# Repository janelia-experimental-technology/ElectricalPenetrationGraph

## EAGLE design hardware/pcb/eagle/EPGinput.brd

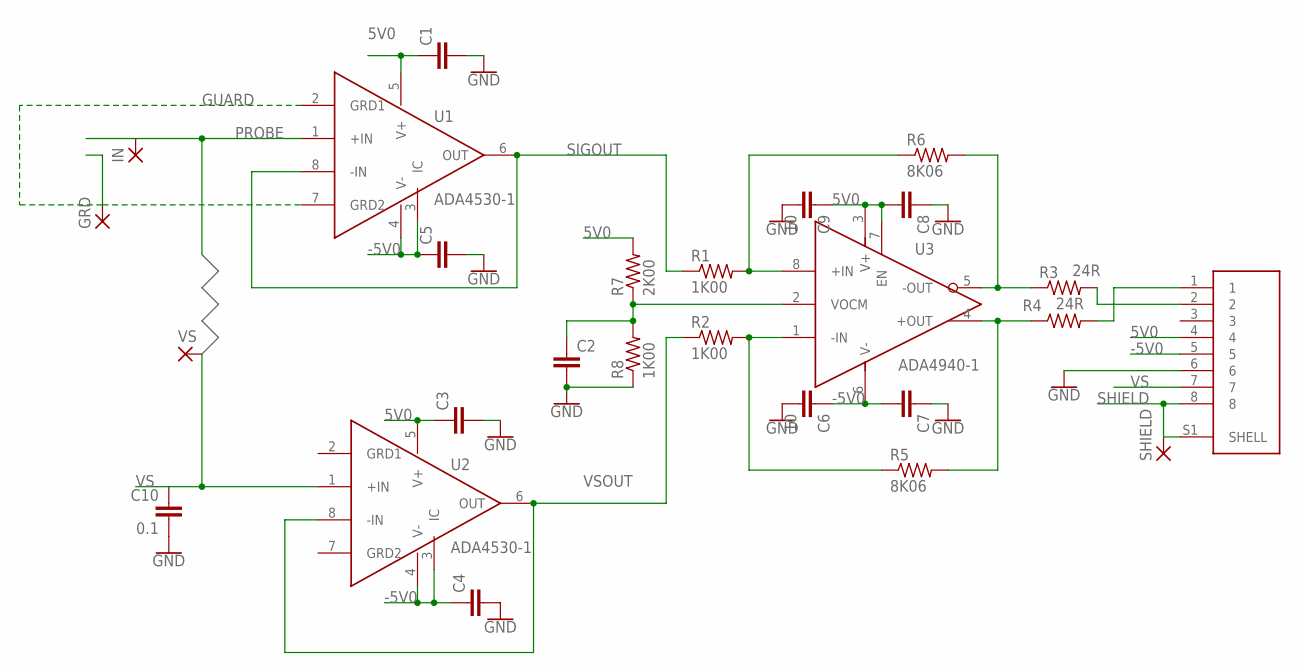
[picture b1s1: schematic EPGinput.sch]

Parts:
C1, C2, C3, C4, C5, C7, C8: CAPS0603S; 0603S
C6, C9: 10; 1206S
C10: 0.1; 0603S
GRD: 2,15/1,0
IN: SMD2; SMD1,27-2,54
J1: 54-00248; TENSILITY_54-00248
R1, R2, R8: 1K00; 0805S
R3, R4: 24R; 0805S
R5, R6: 8K06; 0805S
R7: 2K00; 0805S
SHIELD: 2,15/1,0
U1, U2: ADA4530-1; SOIC-8
U3: ADA4940-1; SOIC-8
VS: 2,15/1,0

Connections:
5V0: C1.1, C3.1, C8.2, C9.1, J1.4, R7.2, U1.5 (V+), U2.5 (V+), U3.3 (V+), U3.7 (EN)
-5V0: C4.1, C5.1, C6.1, C7.2, J1.5, U1.3 (IC), U1.4 (V-), U2.3 (IC), U2.4 (V-), U3.6 (V-)
GND: C1.2, C2.2, C3.2, C4.2, C5.2, C6.2, C7.1, C8.1, C9.2, C10.2, J1.6, R8.1
GUARD: GRD.1, U1.2 (GRD1), U1.7 (GRD2)
unnamed: C2.1, R7.1, R8.2, U3.2 (VOCM)
unnamed: R1.2, R6.1, U3.8 (+IN)
unnamed: R2.2, R5.1, U3.1 (-IN)
unnamed: J1.2, R3.2
unnamed: J1.1, R4.2
unnamed: R4.1, R5.2, U3.4 (+OUT)
unnamed: R3.1, R6.2, U3.5 (-OUT)
PROBE: IN.1, U1.1 (+IN)
SHIELD: J1.8, J1.S1 (SHELL), SHIELD.1
SIGOUT: R1.1, U1.6 (OUT), U1.8 (-IN)
VS: C10.1, J1.7, U2.1 (+IN), VS.1
VSOUT: R2.1, U2.6 (OUT), U2.8 (-IN)

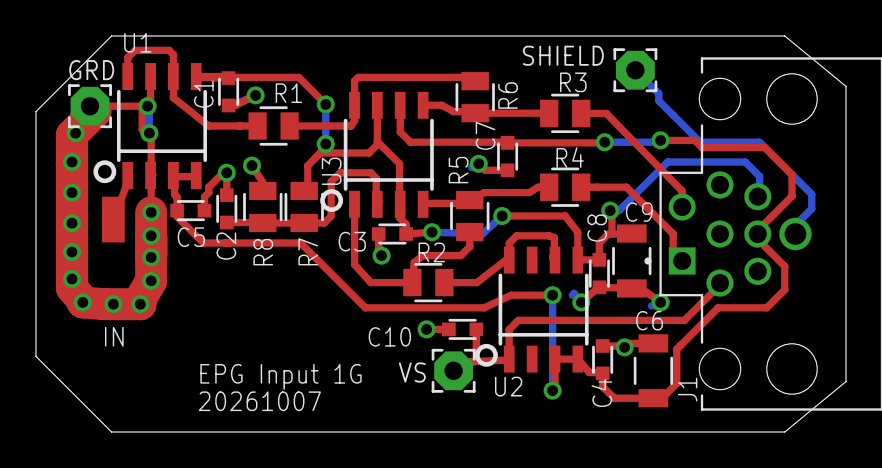
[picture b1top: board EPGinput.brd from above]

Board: 2 copper layers, 45.0 x 22.0 mm, 27 parts (0 on the bottom side), 16 nets.

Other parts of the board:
U$1: POMONA2397

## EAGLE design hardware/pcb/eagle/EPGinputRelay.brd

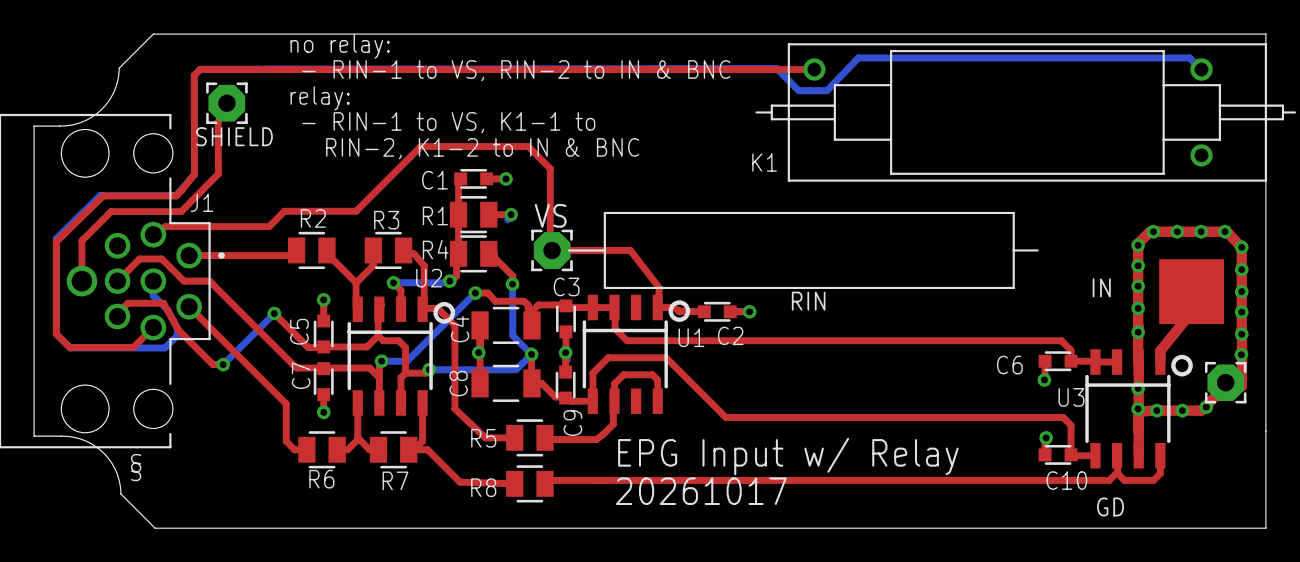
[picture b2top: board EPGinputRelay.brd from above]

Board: 2 copper layers, 72.3 x 29.0 mm, 29 parts (0 on the bottom side), 18 nets.

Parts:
C1, C3, C5, C6, C7, C9, C10: 0603S
C2: 0.1; 0603S
C4, C8: 10; 1206S
GD: 2,15/1,0
IN: PAD-150SQ
J1: 54-00248; TENSILITY_54-00248
K1: REED-RELAY; MRE05
R1, R2, R3, R4, R5, R6, R7, R8: 0805S
RIN: 1GRES
SHIELD: 2,15/1,0
U1, U3: ADA4530-1; SOIC-8
U2: ADA4940-1; SOIC-8
U$1: BNC
VS: 2,15/1,0

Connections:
5V0: C5.1, C8.1, C9.2, C10.1, J1.4, R4.2, U1.5, U2.3, U2.7, U3.5
-5V0: C3.1, C4.1, C6.1, C7.2, J1.5, U1.3, U1.4, U2.6, U3.3, U3.4
GND: C1.2, C2.2, C3.2, C4.2, C5.2, C6.2, C7.1, C8.2, C9.1, C10.2, J1.6, R1.1
GUARD: GD.1, K1.GUARD, U3.2, U3.7
unnamed: J1.S1, SHIELD.1
unnamed: R7.1, R8.2, U2.8
unnamed: R3.1, R5.2, U2.1
unnamed: J1.2, R6.2
unnamed: J1.1, R2.2
unnamed: R2.1, R3.2, U2.4
unnamed: R6.1, R7.2, U2.5
PROBE: IN.P$1, U3.1
RLY+: J1.3, K1.COIL2
RLY-: J1.8, K1.COIL1
SIGOUT: R8.1, U3.6, U3.8
VCOM: C1.1, R1.2, R4.1, U2.2
VS: C2.1, J1.7, U1.1, VS.1
VSOUT: R5.1, U1.6, U1.8

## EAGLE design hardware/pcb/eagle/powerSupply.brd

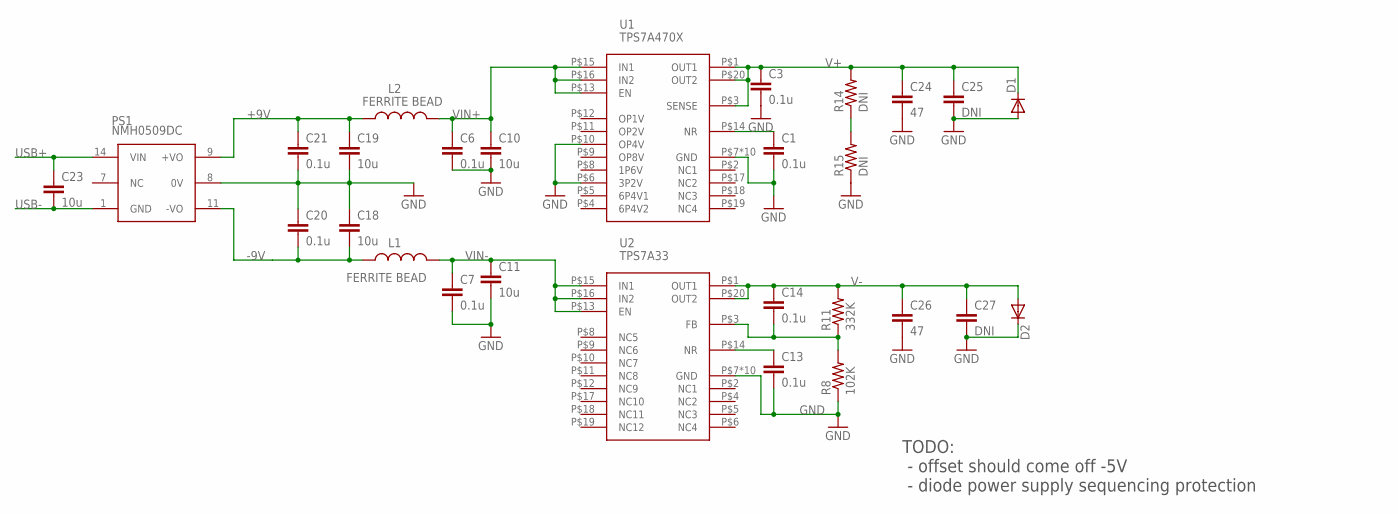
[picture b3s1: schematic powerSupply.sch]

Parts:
C1, C3, C6, C7, C13, C14, C20, C21: 0.1u; 0603S
C10, C11, C18, C19, C23: 10u; C1206
C24, C26: 47; C1206
C25, C27: DNI; C1206
D1, D2: DIODESMA; SMA-DIODE
L1, L2: FERRITE BEAD; 0805S
PS1: NMH0509DC; PDM2
R8: 102K; R0805
R11: 332K; R0805
R14, R15: DNI; R0805
U1: TPS7A470X; VQFN-20-5X5
U2: TPS7A33; VQFN-20-5X5

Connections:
+9V: C19.1, C21.1, L2.1, PS1.9 (+VO)
-9V: C18.2, C20.2, L1.1, PS1.11 (-VO)
GND: C1.2, C3.2, C6.2, C7.2, C10.2, C11.2, C13.2, C18.1, C19.2, C20.1, C21.2, C24.2, C25.2, C26.2, C27.2, D1.A, D2.C, PS1.8 (0V), R8.1, R15.1, U1.P$6 (3P2V), U1.P$7 (GND), U1.P$10 (OP4V), U1.PAD1 (GND), U1.PAD2 (GND), U1.PAD3 (GND), U1.PAD4 (GND), U1.PAD5 (GND), U1.PAD6 (GND), U1.PAD7 (GND), U1.PAD8 (GND), U1.PAD9 (GND), U2.P$7 (GND), U2.PAD1 (GND), U2.PAD2 (GND), U2.PAD3 (GND), U2.PAD4 (GND), U2.PAD5 (GND), U2.PAD6 (GND), U2.PAD7 (GND), U2.PAD8 (GND), U2.PAD9 (GND)
unnamed: C14.2, R8.2, R11.1, U2.P$3 (FB)
unnamed: R14.1, R15.2
unnamed: C13.1, U2.P$14 (NR)
unnamed: C1.1, U1.P$14 (NR)
USB+: C23.1, PS1.14 (VIN)
USB-: C23.2, PS1.1 (GND)
V+: C3.1, C24.1, C25.1, D1.C, R14.2, U1.P$1 (OUT1), U1.P$3 (SENSE), U1.P$20 (OUT2)
V-: C14.1, C26.1, C27.1, D2.A, R11.2, U2.P$1 (OUT1), U2.P$20 (OUT2)
VIN+: C6.1, C10.1, L2.2, U1.P$13 (EN), U1.P$15 (IN1), U1.P$16 (IN2)
VIN-: C7.1, C11.1, L1.2, U2.P$13 (EN), U2.P$15 (IN1), U2.P$16 (IN2)

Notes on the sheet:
TODO: - offset should come off -5V - diode power supply sequencing protection

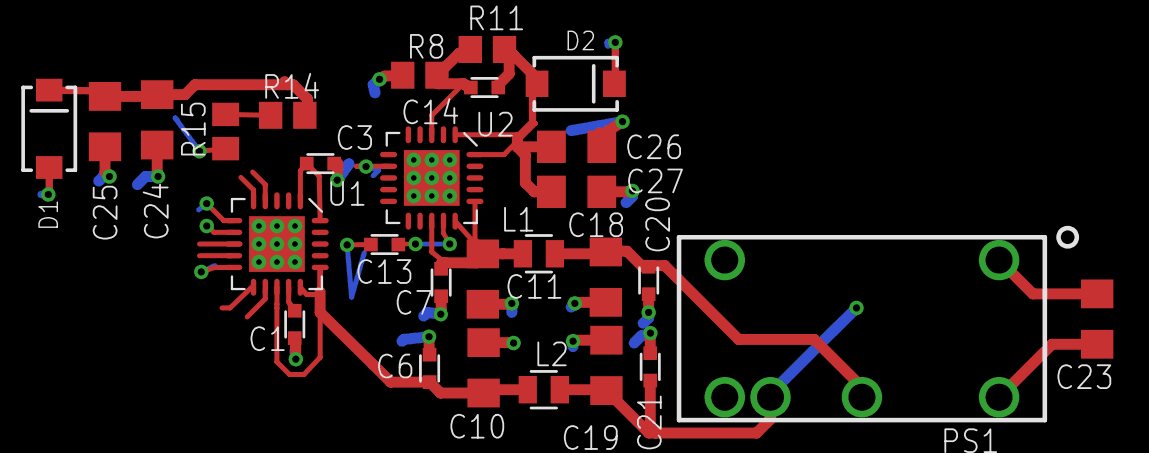
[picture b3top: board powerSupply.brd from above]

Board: 2 copper layers, 28 parts (0 on the bottom side), 13 nets.

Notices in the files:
parts and their libraries:
SparkFun-PowerSymbols: Licensing: Creative Commons ShareAlike 4.0 International - https://creativecommons.org/licenses/by-sa/4.0
